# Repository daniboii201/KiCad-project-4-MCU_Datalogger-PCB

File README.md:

# KiCad project #4: MCU Datalogger PCB
This is my fourth PCB design created using KiCad. Unlike my previous projects, this design focuses on building a microcontroller-based datalogger circuit. The board is intended for logging sensor data to external storage, making it useful for IoT and embedded applications. This project includes two PCB versions: a 2-layer design for cost efficiency and a 4-layer design for improved signal integrity and compact routing.

## Features
• Microcontroller-based datalogger for sensor data acquisition

• Support for external storage (microSD card interface)

• Power regulation for stable MCU operation

• Two PCB versions: 2-layer (budget-friendly) and 4-layer (optimized for EMI and routing)

• Designed for low-power applications and modular sensor connectivity

### Components
• Microcontroller: ATmega328P-AU

• EEPROM: 2 x 24LC2025

• Real-Time Clock: DS1337S_T_R

• Oscillators:

  – 32.768 kHz (RTC timing)

  – 16 MHz (MCU clock)

• Capacitors:

  – 2 x 22 pF
  
  – 2 x 0.1 µF
  
  – 1 x 100 nF
  
• Resistors:

  – 3 x 10 kΩ
  
  – 2 x 4.7 kΩ
  
  – 2 x 330 Ω
  
• LEDs: 2 for status indication

• Battery: For RTC backup

• Pin headers: For programming and sensor interfaces

### Characteristics:
• Two PCB versions:

  – 2-layer: Cost-effective design for basic applications, suitable for simple routing and lower manufacturing costs.

  – 4-layer: Optimized for signal integrity with dedicated ground and power planes, reduced EMI, and improved reliability. Includes mostly SMD components for a compact footprint, silkscreen labels for easy assembly, mounting holes for stability, and copper pours for thermal management.

### How It Works:
The MCU Datalogger PCB is designed to collect sensor data, process it, and store it reliably. Here’s the workflow:

1. Power Management

The board includes a voltage regulator that converts the input supply (battery or external source) to a stable 3.3 V or 5 V rail for the microcontroller and peripherals. Decoupling capacitors near the MCU and SD card ensure clean power and reduce noise.

2. Data Acquisition

Sensors connect via standard interfaces such as I²C, SPI, or UART. The microcontroller periodically reads sensor values based on programmed intervals or triggers.

3. Data Logging

The MCU writes the collected data to a microSD card using the SPI protocol. This allows large storage capacity and easy data retrieval for analysis.

4. Clock & Timing

A crystal oscillator provides accurate timing for logging intervals and communication protocols, ensuring data consistency.

5. PCB Layer Benefits

  • 2-layer version: Simple and cost-effective, suitable for basic applications.

  • 4-layer version: Includes dedicated ground and power planes for better signal integrity, reduced EMI, and improved reliability in noisy environments.

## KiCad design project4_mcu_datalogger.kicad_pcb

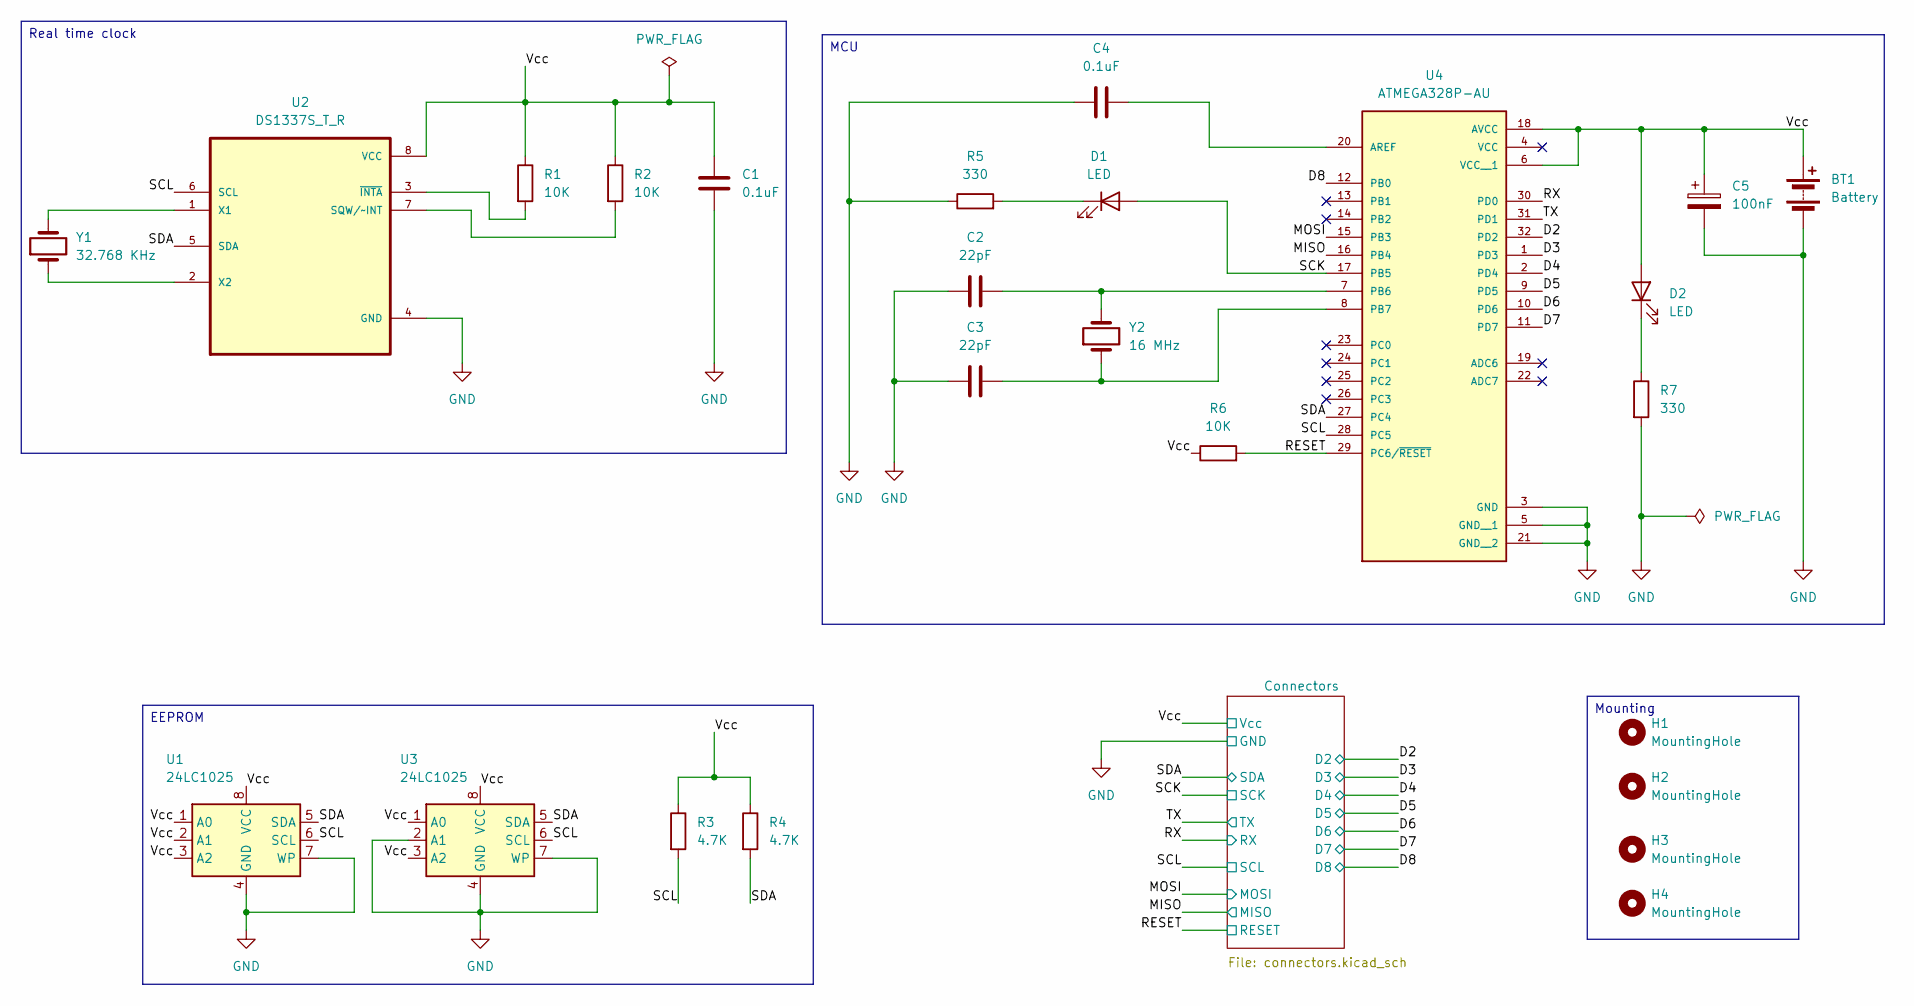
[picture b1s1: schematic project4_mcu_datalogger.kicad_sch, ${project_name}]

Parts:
BT1: Battery; PinHeader_1x02_P2.54mm_Vertical
C1, C4: 0.1uF; C_0805_2012Metric
C2, C3: 22pF; C_0805_2012Metric
C5: 100nF; C_0805_2012Metric
D1, D2: LED; LED_0805_2012Metric
H1, H2, H3, H4: MountingHole; MountingHole_2.1mm
R1, R2, R6: 10K; R_0805_2012Metric
R3, R4: 4.7K; R_0805_2012Metric
R5, R7: 330; R_0805_2012Metric
U1, U3: 24LC1025; SOIC-8_5.3x5.3mm_P1.27mm
U2: DS1337S_T_R; SOIC127P600X175-8N
U4: ATMEGA328P-AU; QFP80P900X900X120-32N; PARTREV 8271A
Y1: 32.768 KHz; Crystal_SMD_Abracon_ABM3-2Pin_5.0x3.2mm_HandSoldering
Y2: 16 MHz; Crystal_SMD_Abracon_ABM3-2Pin_5.0x3.2mm_HandSoldering

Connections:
/D2: U4.32 (PD2); also elsewhere on the board
/D3: U4.1 (PD3); also elsewhere on the board
/D4: U4.2 (PD4); also elsewhere on the board
/D5: U4.9 (PD5); also elsewhere on the board
/D6: U4.10 (PD6); also elsewhere on the board
/D7: U4.11 (PD7); also elsewhere on the board
/D8: U4.12 (PB0); also elsewhere on the board
/MISO: U4.16 (PB4); also elsewhere on the board
/MOSI: U4.15 (PB3); also elsewhere on the board
/RESET: R6.2, U4.29 (PC6/~RESET); also elsewhere on the board
/RX: U4.30 (PD0); also elsewhere on the board
/SCK: D1.2 (A), R3.2, U1.6 (SCL), U2.6 (SCL), U3.6 (SCL), U4.17 (PB5), U4.28 (PC5); also elsewhere on the board
/SDA: R4.2, U1.5 (SDA), U2.5 (SDA), U3.5 (SDA), U4.27 (PC4); also elsewhere on the board
/TX: U4.31 (PD1); also elsewhere on the board
/Vcc: BT1.1 (+), C1.1, C5.1, D2.2 (A), R1.1, R2.1, R3.1, R4.1, R6.1, U1.1 (A0), U1.2 (A1), U1.3 (A2), U1.8 (VCC), U2.8 (VCC), U3.1 (A0), U3.3 (A2), U3.8 (VCC), U4.6 (VCC__1), U4.18 (AVCC); also elsewhere on the board
GND: BT1.2 (-), C1.2, C2.1, C3.1, C4.1, C5.2, R5.1, R7.2, U1.4 (GND), U1.7 (WP), U2.4 (GND), U3.2 (A1), U3.4 (GND), U3.7 (WP), U4.3 (GND), U4.5 (GND__1), U4.21 (GND__2); also elsewhere on the board
unnamed: D1.1 (K), R5.2
unnamed: D2.1 (K), R7.1
unnamed: R2.2, U2.7 (SQW/~INT)
unnamed: U2.1 (X1), Y1.2
unnamed: U2.2 (X2), Y1.1
unnamed: R1.2, U2.3 (~INTA)
unnamed: C4.2, U4.20 (AREF)
unnamed: C2.2, U4.7 (PB6), Y2.2
unnamed: C3.2, U4.8 (PB7), Y2.1

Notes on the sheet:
MCU
EEPROM
Real time clock
Mounting

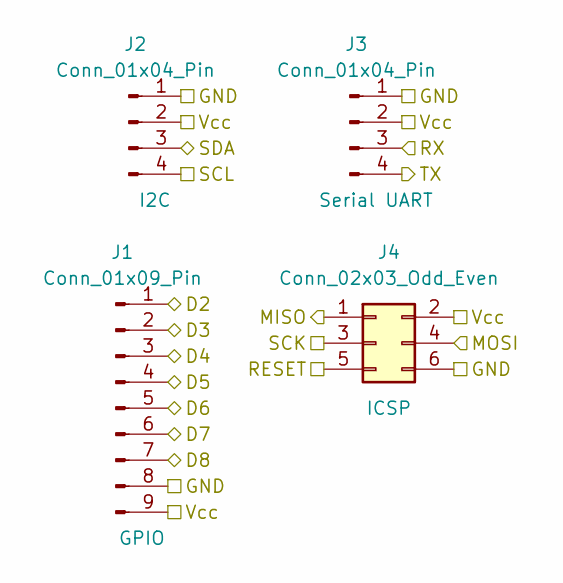
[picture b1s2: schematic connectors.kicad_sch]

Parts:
J1: Conn_01x09_Pin; PinHeader_1x09_P2.54mm_Vertical
J2, J3: Conn_01x04_Pin; PinHeader_1x04_P2.54mm_Vertical
J4: Conn_02x03_Odd_Even; PinHeader_2x03_P2.54mm_Vertical

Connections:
/D2: J1.1; also elsewhere on the board
/D3: J1.2; also elsewhere on the board
/D4: J1.3; also elsewhere on the board
/D5: J1.4; also elsewhere on the board
/D6: J1.5; also elsewhere on the board
/D7: J1.6; also elsewhere on the board
/D8: J1.7; also elsewhere on the board
/MISO: J4.1; also elsewhere on the board
/MOSI: J4.4; also elsewhere on the board
/RESET: J4.5; also elsewhere on the board
/RX: J3.3; also elsewhere on the board
/SCK: J2.4, J4.3; also elsewhere on the board
/SDA: J2.3; also elsewhere on the board
/TX: J3.4; also elsewhere on the board
/Vcc: J1.9, J2.2, J3.2, J4.2; also elsewhere on the board
GND: J1.8, J2.1, J3.1, J4.6; also elsewhere on the board

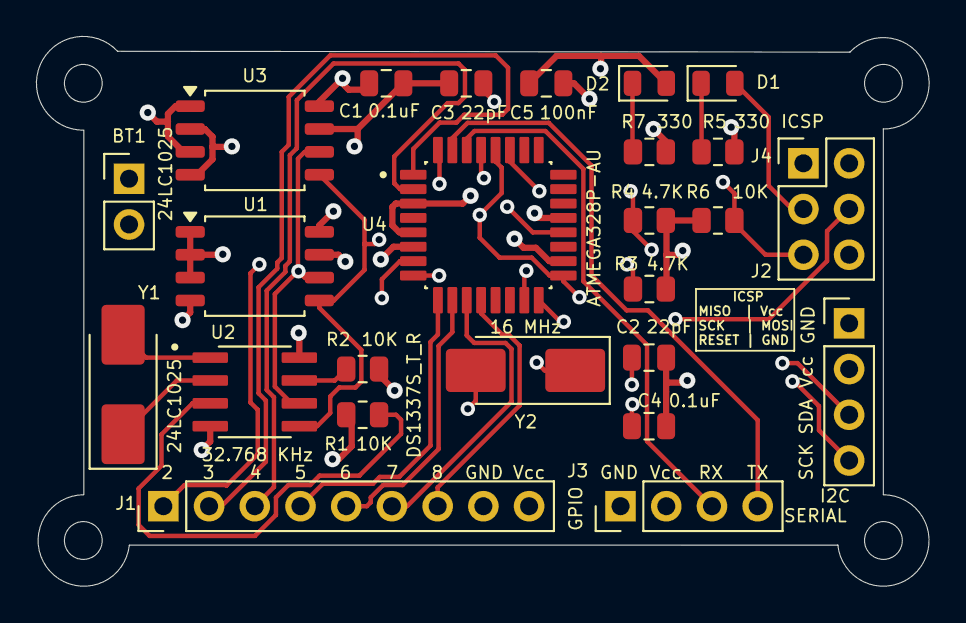
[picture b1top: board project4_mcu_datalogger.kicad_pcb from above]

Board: 4 copper layers, 49.6 x 30.5 mm, 29 parts (0 on the bottom side), 25 nets.

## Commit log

2025-11-28 Update .gitignore to ignore gerbers folder
2025-11-28 Update .gitignore to ignore gerbers and backups folders
2025-11-28 Remove Gerber folder from repo but keep locally
2025-12-01 commit .kicad_pro
2025-12-01 update .gitignore to exclude cache files
2025-12-01 Setup of EEschema for new project
2025-12-01 Have added required symbols to the schematic sheets
2025-12-01 Changed locations of symbols
2025-12-01 Added component values
2025-12-02 Completed symbol to footprint associations
2025-12-02 Completed wiring of main sheet
2025-12-02 Completed wiring in the second sheet
2025-12-02 Allocated GND and Vcc nets to the Power net class
2025-12-02 Completed comments
2025-12-03 Setup Pcbnew
2025-12-03 Completed placement of footprints
2025-12-05 Completed PCB routing
2025-12-05 Rework of PCB routing
2025-12-05 Added copper fills and improved routing
2025-12-08 Fixed outstanding issues
2025-12-08 Added back silkscreen
2025-12-08 Added missing 3d models to components
2025-12-12 Completed 4-layer pcb routing
2025-12-12 Completed v2 of pcb routing
2025-12-12 Added gitattributes file to ignore PCB files during merge
2025-12-12 Fixed two defects in the schematic
2025-12-15 Fixed bugs and completed 2-layer PCB
2025-12-18 Fixed net bugs in 4-layer version of the PCB
2025-12-18 Completed 4-layer pcb
2025-12-18 README_v1
2025-12-18 README v2
